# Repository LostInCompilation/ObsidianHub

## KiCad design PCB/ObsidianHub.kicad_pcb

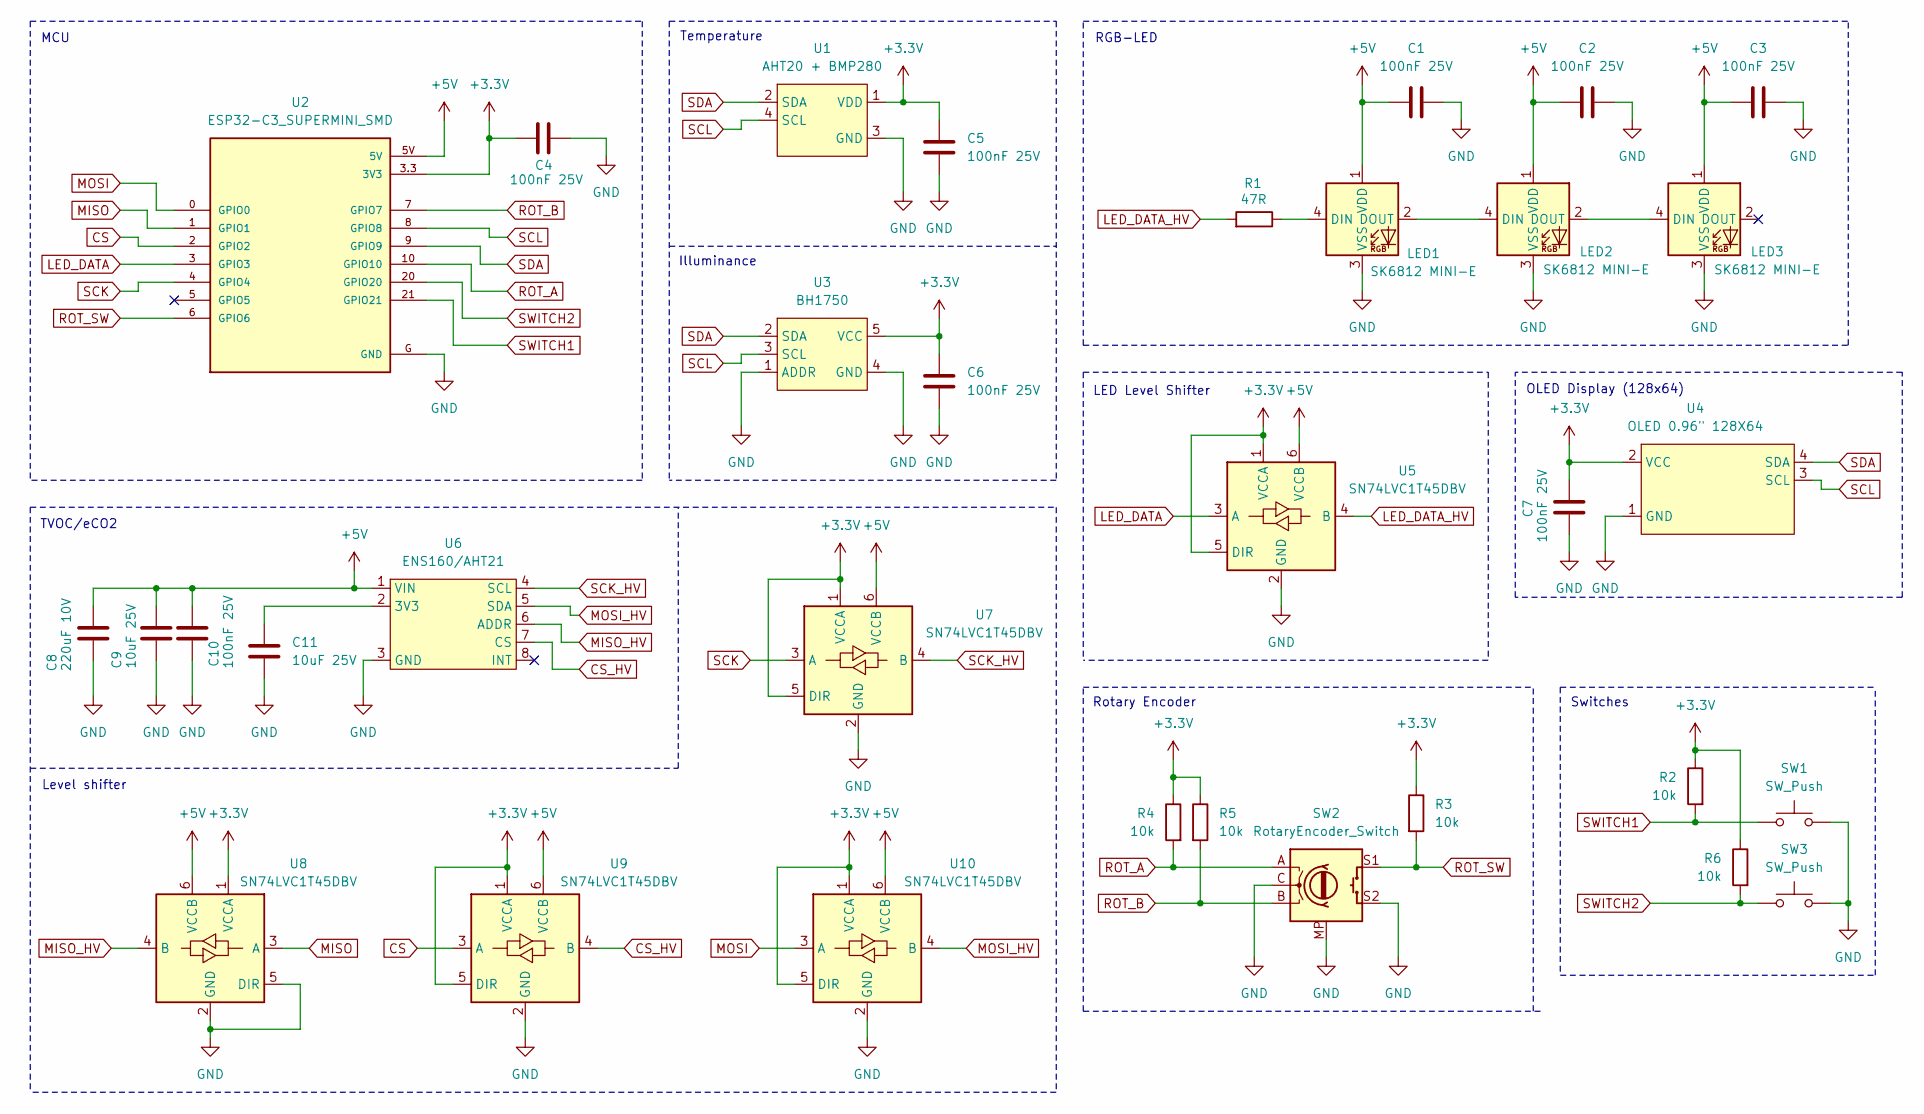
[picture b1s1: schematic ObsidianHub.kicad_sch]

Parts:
C1, C2, C3, C4, C5, C6, C7, C10: 100nF 25V; C_1206_3216Metric_Pad1.33x1.80mm_HandSolder
C8: 220uF 10V; C_Radial_D6.3mm_H7.0mm_P2.50mm
C9, C11: 10uF 25V; C_1206_3216Metric_Pad1.33x1.80mm_HandSolder
LED1, LED2, LED3: SK6812 MINI-E; LED SK6812-MINI-E Cutout
R1: 47R; R_1206_3216Metric_Pad1.30x1.75mm_HandSolder
R2, R3, R4, R5, R6: 10k; R_1206_3216Metric_Pad1.30x1.75mm_HandSolder
SW1, SW3: SW_Push; SW_Cherry_MX_PCB_1.00u
SW2: RotaryEncoder_Switch; RotaryEncoder_Alps_EC11E-Switch_Vertical_H20mm
U1: AHT20 + BMP280; MODULE_AHT20_BMP280
U2: ESP32-C3_SUPERMINI_SMD; MODULE_ESP32-C3_SUPERMINI
U3: BH1750
U4: OLED 0.96" 128X64; OLED 0.96 128x64
U5, U7, U8, U9, U10: SN74LVC1T45DBV; SOT-23-6
U6: ENS160/AHT21; ENS160_AHT21_Module

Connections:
+3.3V: C4.1, C5.1, C6.1, C7.1, R2.1, R3.1, R4.1, R5.1, R6.1, U1.1 (VDD), U2.3.3 (3V3), U3.5 (VCC), U4.2 (VCC), U5.1 (VCCA), U5.5 (DIR), U7.1 (VCCA), U7.5 (DIR), U8.1 (VCCA), U9.1 (VCCA), U9.5 (DIR), U10.1 (VCCA), U10.5 (DIR)
+5V: C1.1, C2.1, C3.1, C8.1, C9.1, C10.1, LED1.1 (VDD), LED2.1 (VDD), LED3.1 (VDD), U2.5V, U5.6 (VCCB), U6.1 (VIN), U7.6 (VCCB), U8.6 (VCCB), U9.6 (VCCB), U10.6 (VCCB)
CS: U2.2 (GPIO2), U9.3 (A)
CS_HV: U6.7 (CS), U9.4 (B)
GND: C1.2, C2.2, C3.2, C4.2, C5.2, C6.2, C7.2, C8.2, C9.2, C10.2, C11.2, LED1.3 (VSS), LED2.3 (VSS), LED3.3 (VSS), SW1.2, SW2.C, SW2.MP, SW2.S2, SW3.2, U1.3 (GND), U2.G (GND), U3.1 (ADDR), U3.4 (GND), U4.1 (GND), U5.2 (GND), U6.3 (GND), U7.2 (GND), U8.2 (GND), U8.5 (DIR), U9.2 (GND), U10.2 (GND)
LED_DATA: U2.3 (GPIO3), U5.3 (A)
LED_DATA_HV: R1.2, U5.4 (B)
MISO: U2.1 (GPIO1), U8.3 (A)
MISO_HV: U6.6 (ADDR), U8.4 (B)
MOSI: U2.0 (GPIO0), U10.3 (A)
MOSI_HV: U6.5 (SDA), U10.4 (B)
unnamed: LED1.4 (DIN), R1.1
unnamed: LED1.2 (DOUT), LED2.4 (DIN)
unnamed: LED2.2 (DOUT), LED3.4 (DIN)
unnamed: C11.1, U6.2 (3V3)
ROT_A: R4.2, SW2.A, U2.10 (GPIO10)
ROT_B: R5.2, SW2.B, U2.7 (GPIO7)
ROT_SW: R3.2, SW2.S1, U2.6 (GPIO6)
SCK: U2.4 (GPIO4), U7.3 (A)
SCK_HV: U6.4 (SCL), U7.4 (B)
SCL: U1.4 (SCL), U2.8 (GPIO8), U3.3 (SCL), U4.3 (SCL)
SDA: U1.2 (SDA), U2.9 (GPIO9), U3.2 (SDA), U4.4 (SDA)
SWITCH1: R2.2, SW1.1, U2.21 (GPIO21)
SWITCH2: R6.2, SW3.1, U2.20 (GPIO20)

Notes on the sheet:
RGB-LED
Temperature
Illuminance
TVOC/eCO2
Rotary Encoder
MCU
Switches
Level shifter
LED Level Shifter
OLED Display (128x64)

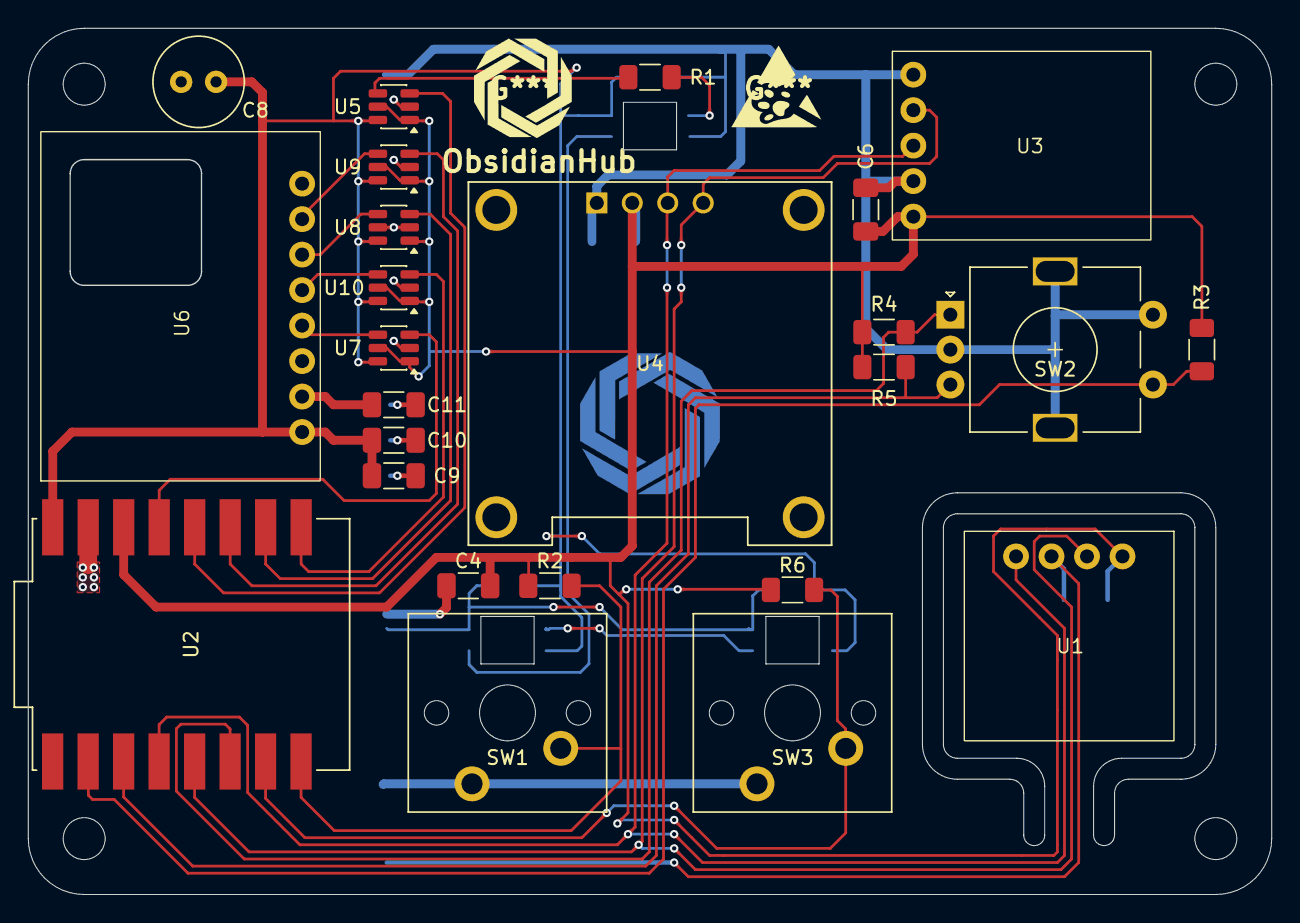
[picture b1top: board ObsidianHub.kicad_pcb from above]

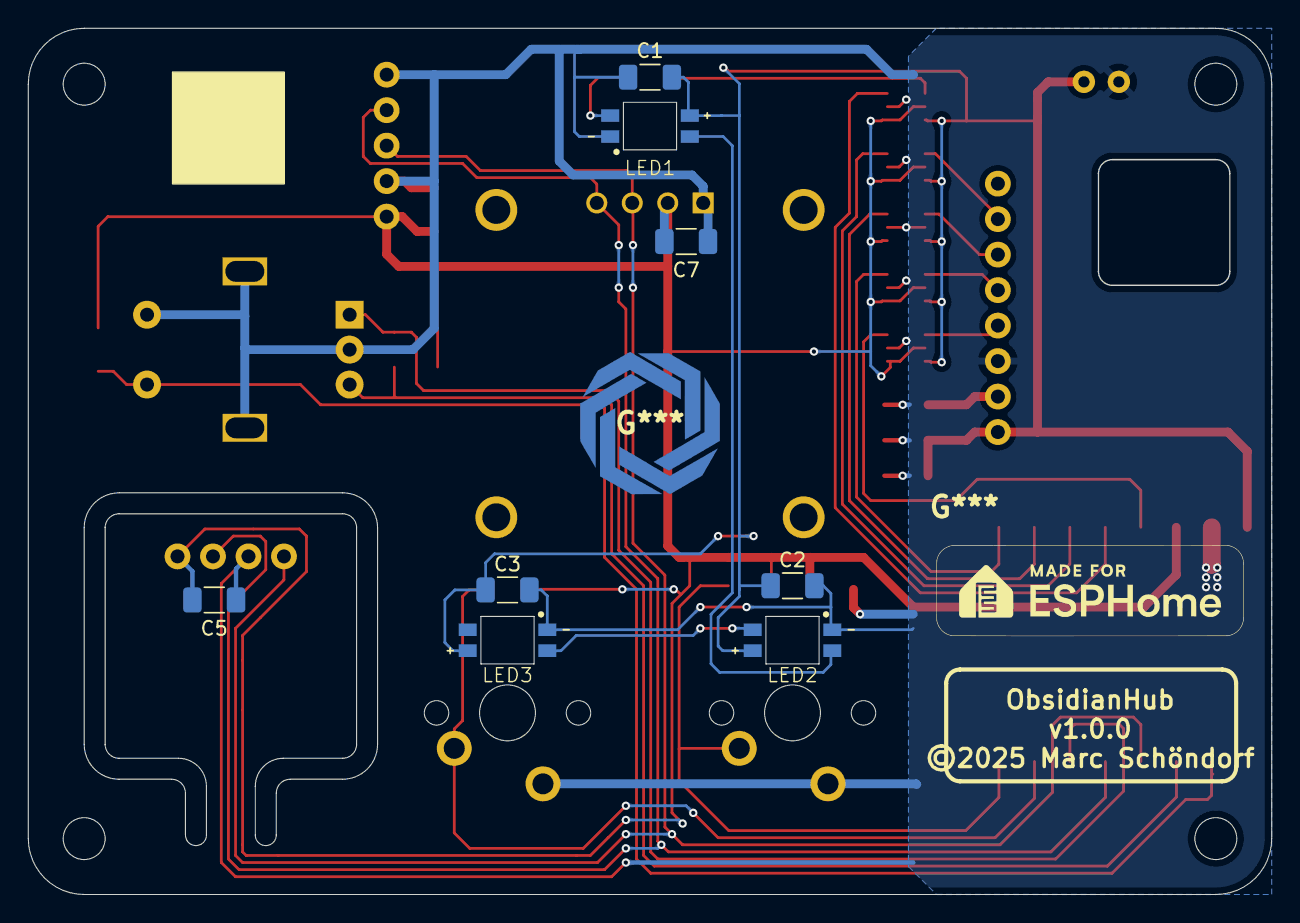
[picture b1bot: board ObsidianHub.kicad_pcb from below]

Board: 2 copper layers, 89.0 x 62.0 mm, 33 parts (8 on the bottom side), 24 nets.

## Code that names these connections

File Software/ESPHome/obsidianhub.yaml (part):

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i2c:
  id: i2c_bus
  sda:
    number: GPIO9
    ignore_strapping_warning: true
  scl:
    number: GPIO8
    ignore_strapping_warning: true
  scan: false
  frequency: 400kHz
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###############################################################
spi:
  id: spi_bus
  clk_pin: GPIO4
  mosi_pin: GPIO0
  miso_pin: GPIO1

###############################################################
# Global Variables
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    name: "All LEDs"
    id: led_strip_controller
    rgb_order: GRB
    pin: GPIO3
    num_leds: 3
    chipset: SK6812
    max_refresh_rate: 12ms
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  # ENS160: Air quality sensor (eCO2, TVOC, AQI)
  - platform: ens160_spi
    cs_pin:
      number: GPIO2
      ignore_strapping_warning: true
    data_rate: 200kHz
    update_interval: 10s
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    name: "Rotary Encoder"
    id: encoder_input
    pin_a:
      number: GPIO7
      inverted: true
    pin_b:
      number: GPIO10
      inverted: true
    min_value: 0
    max_value: 100
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  # Left tactile button
  - platform: gpio
    pin:
      number: GPIO21
      inverted: true
    name: "Button Left"
    id: button_left
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  # Right tactile button
  - platform: gpio
    pin:
      number: GPIO20
      inverted: true
    name: "Button Right"
    id: button_right
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  # Rotary encoder push button
  - platform: gpio
    pin:
      number: GPIO6
      inverted: true
    name: "Button Encoder"
    id: button_encoder
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
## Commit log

2025-12-12 Sdded status LED behaviour on wifi setup/disconnect
2025-12-12 UI improvements
2025-12-12 Set correct version
2025-12-12 Version test
2025-12-12 Switch to online files
2025-12-12 Use secrets
2025-12-12 Automatic updates
2025-12-13 Fix page switching logic
2025-12-13 Added missing font
2025-12-13 Removed debug component
2025-12-14 LED work
2025-12-14 Version
2025-12-15 Code cleanup
2025-12-16 Added weather and location fetching (json parsing), added selection which components should go to sleep (display/LEDs), fixed bug where leds would fade out after display went to sleep, started weathe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
2025-12-16 Cleanup location and weather fetching
2025-12-16 Changelog
2025-12-16 Added system monitor python script
2025-12-16 Update tests
2025-12-16 Implemented later button on update available page
2025-12-16 Updated JSON parsing to use typesafe functions
2025-12-16 Remove test code
2025-12-16 Weather dashboard work
2025-12-16 Cleanup
2025-12-16 Weather icons
2025-12-17 Started scrolling weather ticker implementation
2025-12-17 Switched to fixed size integers
2025-12-17 Enable user specific updates, LED optimizations
2025-12-17 Reshow update available if user pressed later button
2025-12-17 Fixed display flicker on reboot, removed deprecated YAML syntax
2025-12-17 Show rebooting page after update finished
2025-12-17 v1.1.0
2025-12-17 v1.1.0 main binary
2025-12-18 v1.1.0 binary
2025-12-18 Removed old files
2025-12-18 Adjusted intervals
2025-12-19 Implemented auto dim function
2025-12-19 v1.1.1 release
2025-12-19 Enable auto sleep on update available page
2025-12-21 Begin implementation of custom notifications with automatic scrolling, bug fixes
2025-12-22 Fixed formatting, notification page work and auto sleep and dimming bug fixes
2025-12-22 Rewrote notification page
2025-12-23 Added cubic bezier easing to scrolling notification message
2025-12-23 Added support for displaying notifications while on update available page
2025-12-24 Notification message scrolling work
2025-12-24 Version test, Changelog
2025-12-25 Optimized boot logo, changelog
2025-12-25 Boot animation optimized
2025-12-25 Made notification message scroll easing independent from message length, added automatic timezone fetching from IP
2025-12-26 Scrolling optimizations
2025-12-26 Added Fusion360 file for ObsidianHub (full CAD)
2025-12-27 Optimizations and renaming
2025-12-29 removed test code
2026-01-04 Update year
2026-01-04 Reworked notification message word wrapping, scrolling and rendering. Switched to char arrays as buffers instead of STL
2026-01-04 Update image
2026-01-05 Optimize notification word wrapping algorithm
2026-01-07 Optimize word wrapping
2026-01-07 Cleanup & optimize notification page code
2026-01-08 Optimize notification rendering, changed variable names
2026-01-08 Small changes to notification rendering
2026-01-08 Removed unneeded clamping
2026-01-09 Reworked Uptime Menu Entry Scrolling
2026-01-09 Added total device-on-time counter, small changes, CHANGELOG
2026-01-09 Small optimizations
2026-01-10 Optimizations, finishing v1.2.0
2026-01-10 v1.2.0 release
2026-01-11 Update location periodically

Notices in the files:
Software/ESPHome/obsidianhub.yaml:
(C)2026 Marc Schöndorf
--- Copyright Text (About page) ---
PCB/ObsidianHub.kicad_pcb:
©2025 Marc Schöndorf
